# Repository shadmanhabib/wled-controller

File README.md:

# WLED-Controller

## Table of Contents
- [Automated Fuel Card Processing](#automated-fuel-card-processing)
  - [Table of Contents](#table-of-contents)
  - [About The Project](#about-the-project)
  - [Getting Started](#getting-started)
    - [Prerequisites](#prerequisites)
    - [Installation](#installation)
  - [Usage](#usage)
  - [Changelog](#changelog)

## About The Project
PCB design and fabrication of ESP8266 based controller for WLED.

This project contains multiple branches, each with its own unique use case and form factor. This is the main branch which contains the smallest controller with the least number of additional features.

## Getting Started
To get a build this project (or parts thereof), these steps may be followed.

### Prerequisites
1. A download of either the WLED binary or source code that can be compile for upload onto the ESP8266.
2. If you want to make changes to the PCB design or would like to generate new fabrication files, an installation of KiCAD is required.

### Installation
1. Manufacture a PCB.
2. Upload WLED using ESPHomeFlasher or other programs.

## Usage
Examples will be given in future iterations of this file.

_For more examples, please refer to the [Documentation](https://)_

## Changelog
All notable changes to this project will be documented in this section.

The format is based on [Keep a Changelog](https://keepachangelog.com/en/1.0.0/),
and this project attempts to adhere to [Semantic Versioning](https://semver.org/spec/v2.0.0.html).

### [v2.0.0]
#### Changed
- New compact form factor.
- Multiple changes to component selection.
- Removed micro USB port. Replaced with 2.54mm pin header.

#### Added
- Power switching between LiPo and 5V external with external priority.

#### Removed
- Boost converter.

### [v1.0.0]
#### Initial design
- ESP8266 based design.
- Single-cell LiPo charge circuit.
- Boost converter for 5V output.
- Logic level converter (bi-directional 3.3-5V).

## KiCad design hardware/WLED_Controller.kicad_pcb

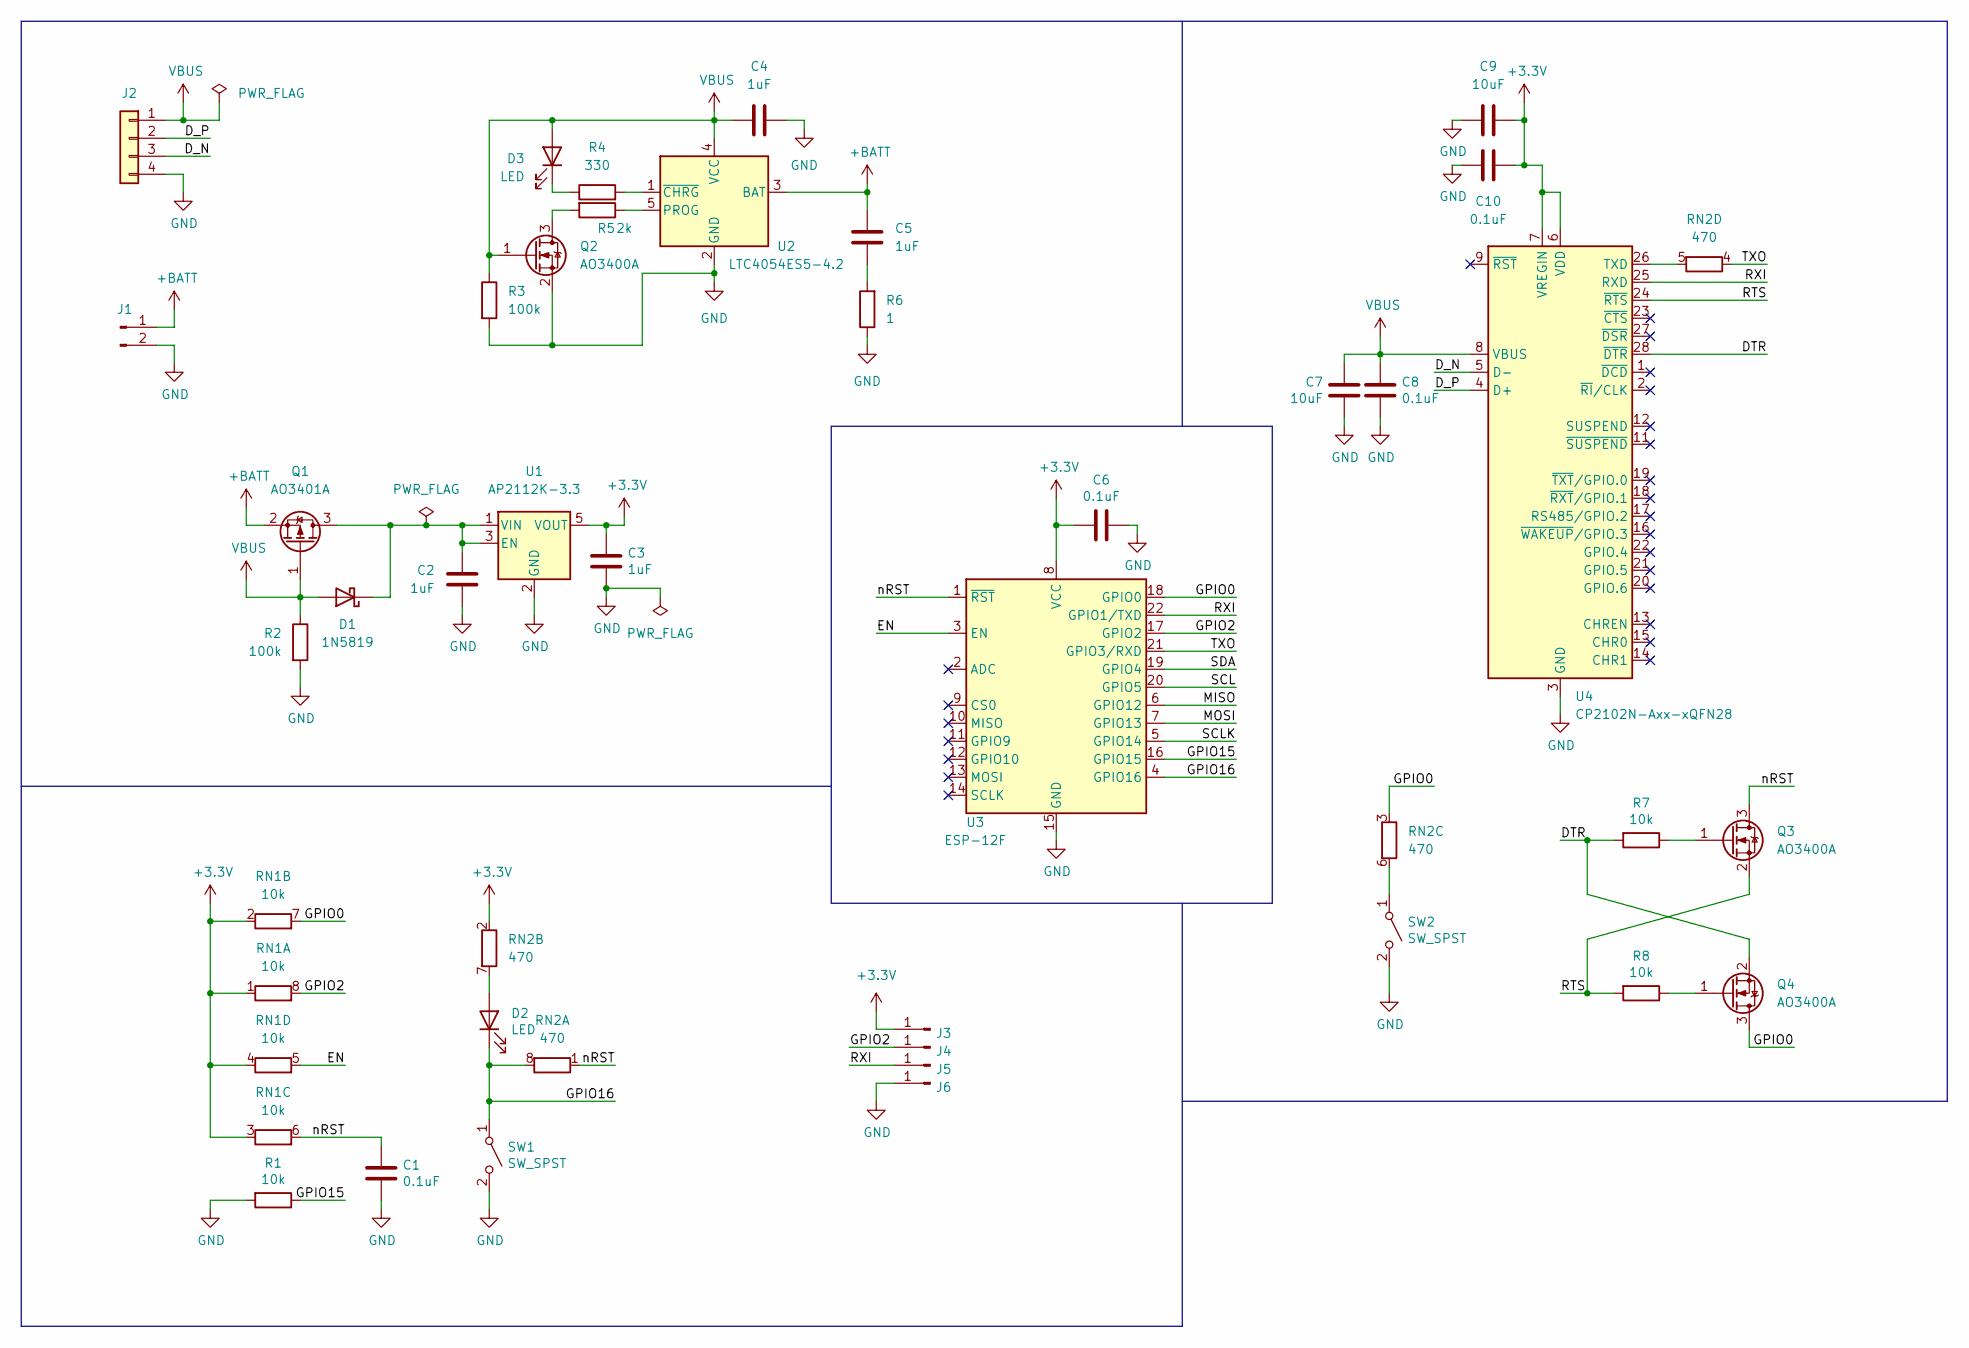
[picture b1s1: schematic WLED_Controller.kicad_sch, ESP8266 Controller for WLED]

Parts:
C1, C6, C8, C10: 0.1uF; C_0603_1608Metric
C2, C3, C4, C5: 1uF; C_0603_1608Metric
C7, C9: 10uF; C_0603_1608Metric
D1: 1N5819; D_SOD-323
D2, D3: LED; LED_0603_1608Metric
J1: Conn_01x02_Male; JST_PH_S2B-PH-K_1x02_P2.00mm_Horizontal
J2: Conn_01x04; PinHeader_1x04_P2.54mm_Vertical
J3, J4, J5, J6: Conn_01x01_Male; SolderWirePad_1x01_SMD_1x2mm
Q1: AO3401A; SOT-23
Q2, Q3, Q4: AO3400A; SOT-23
R1, R7, R8: 10k; R_0603_1608Metric
R2, R3: 100k; R_0603_1608Metric
R4: 330; R_0603_1608Metric
R5: 2k; R_0603_1608Metric
R6: 1; R_0603_1608Metric
RN1: 10k; R_Array_Convex_4x0603
RN2: 470; R_Array_Convex_4x0603
SW1, SW2: SW_SPST; SW_SPST_TL3342
U1: AP2112K-3.3; SOT-23-5
U2: LTC4054ES5-4.2; TSOT-23-5
U3: ESP-12F; ESP-12E
U4: CP2102N-Axx-xQFN28; QFN-28-1EP_5x5mm_P0.5mm_EP3.35x3.35mm

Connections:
+3V3: C3.1, C6.2, C9.1, C10.1, J3.1, RN1.1 (R1.1), RN1.2 (R2.1), RN1.3 (R3.1), RN1.4 (R4.1), RN2.2 (R2.1), U1.5 (VOUT), U3.8 (VCC), U4.6 (VDD), U4.7 (VREGIN)
+BATT: C5.2, J1.1, Q1.2 (S), U2.3 (BAT)
/DTR: Q4.2 (S), R7.2, U4.28 (~DTR)
/D_N: J2.3, U4.5 (D-)
/D_P: J2.2, U4.4 (D+)
/EN: RN1.5 (R4.2), U3.3 (EN)
/GPIO0: Q4.3 (D), RN1.7 (R2.2), RN2.3 (R3.1), U3.18 (GPIO0)
/GPIO2: J4.1, RN1.8 (R1.2), U3.17 (GPIO2)
/GPIO15: R1.1, U3.16 (GPIO15)
/GPIO16: D2.1 (K), RN2.8 (R1.2), SW1.1 (A), U3.4 (GPIO16)
/MISO: U3.6 (GPIO12)
/MOSI: U3.7 (GPIO13)
/RTS: Q3.2 (S), R8.2, U4.24 (~RTS)
/RXI: J5.1, U3.22 (GPIO1/TXD), U4.25 (RXD)
/SCL: U3.20 (GPIO5)
/SCLK: U3.5 (GPIO14)
/SDA: U3.19 (GPIO4)
/TXO: RN2.4 (R4.1), U3.21 (GPIO3/RXD)
/nRST: C1.1, Q3.3 (D), RN1.6 (R3.2), RN2.1 (R1.1), U3.1 (~RST)
GND: C1.2, C2.2, C3.2, C4.2, C6.1, C7.2, C8.2, C9.2, C10.2, J1.2, J2.4, J6.1, Q2.2 (S), R1.2, R2.2, R3.2, R6.1, SW1.2 (B), SW2.2 (B), U1.2 (GND), U2.2 (GND), U3.15 (GND), U4.3 (GND), U4.29 (GND)
unnamed: C2.1, D1.1 (K), Q1.3 (D), U1.1 (VIN), U1.3 (EN)
unnamed: C5.1, R6.2
unnamed: D2.2 (A), RN2.7 (R2.2)
unnamed: D3.1 (K), R4.1
unnamed: Q2.3 (D), R5.2
unnamed: Q3.1 (G), R7.1
unnamed: Q4.1 (G), R8.1
unnamed: R4.2, U2.1 (~CHRG)
unnamed: R5.1, U2.5 (PROG)
unnamed: RN2.5 (R4.2), U4.26 (TXD)
unnamed: RN2.6 (R3.2), SW2.1 (A)
VBUS: C4.1, C7.1, C8.1, D1.2 (A), D3.2 (A), J2.1, Q1.1 (G), Q2.1 (G), R2.1, R3.1, U2.4 (VCC), U4.8 (VBUS)

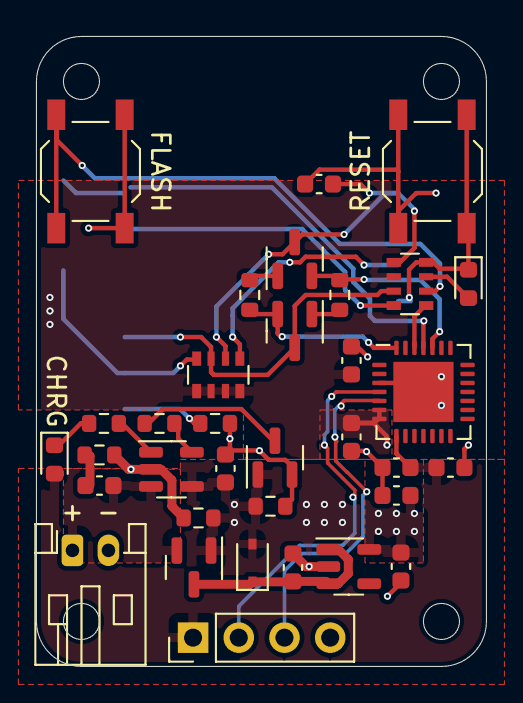
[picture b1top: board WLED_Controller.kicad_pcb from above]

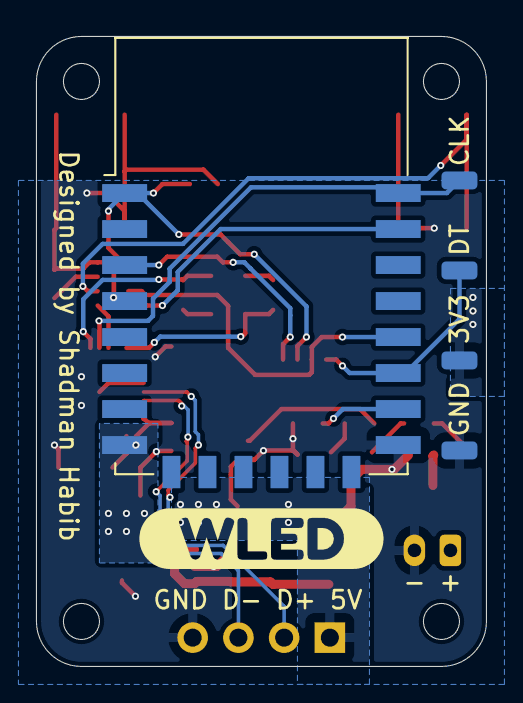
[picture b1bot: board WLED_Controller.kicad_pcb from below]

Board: 2 copper layers, 25.0 x 35.0 mm, 40 parts (6 on the bottom side), 27 nets.

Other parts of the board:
kibuzzard-6350B1D2: G***; kibuzzard-6350B1D2

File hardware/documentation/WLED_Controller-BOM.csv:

Comment,Designator,Footprint,LCSC
0.1uF,"C1,C6,C8,C10",Capacitor_SMD:C_0603_1608Metric,C14663
1uF,"C2,C3,C4,C5",Capacitor_SMD:C_0603_1608Metric,C15849
10uF,"C7,C9",Capacitor_SMD:C_0603_1608Metric,C96446
1N5819,D1,Diode_SMD:D_SOD-323,C191023
LED_blue,D2,LED_SMD:LED_0603_1608Metric,C72041
LED_red,D3,LED_SMD:LED_0603_1608Metric,C2286
AO3401A,Q1,Package_TO_SOT_SMD:SOT-23,C15127
AO3400A,"Q2,Q3,Q4",Package_TO_SOT_SMD:SOT-23,C20917
10k,"R1,R7,R8",Resistor_SMD:R_0603_1608Metric,C25804
100k,"R2,R3",Resistor_SMD:R_0603_1608Metric,C25803
330,R4,Resistor_SMD:R_0603_1608Metric,C23138
2k,R5,Resistor_SMD:R_0603_1608Metric,C17604
1,R6,Resistor_SMD:R_0603_1608Metric,C22936
10k,RN1,Resistor_SMD:R_Array_Concave_4x0603,C29718
470,RN2,Resistor_SMD:R_Array_Concave_4x0603,C25510
SW_SPST,"SW1,SW2",Button_Switch_SMD:SW_SPST_TL3342,C318884
AP2112K-3.3,U1,Package_TO_SOT_SMD:SOT-23-5,C51118
LTC4054ES5-4.2,U2,Package_TO_SOT_SMD:TSOT-23-5,C32574
ESP-12F,U3,RF_Module:ESP-12E,
CP2102N-Axx-xQFN28,U4,Package_DFN_QFN:QFN-28-1EP_5x5mm_P0.5mm_EP3.35x3.35mm,C6568

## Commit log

2022-11-29 First commit
    The first commit contains all the files from v1.0.0 of the PCB design.
2022-11-29 Updated to v2.0.0
    Contains the PCB design and fabrication files for v2.0.0 of the WLED
    controller.
2022-12-09 Updated to v2.0.1
    Addition of PCB silkscreen and updates to project README.
